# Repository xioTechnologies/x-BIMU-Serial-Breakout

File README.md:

x-BIMU-Serial-Breakout
======================

x-BIMU serial breakout board

* FTDI compatible 6-way male header (x-BIMU UART inputs are 5 V tolerant)
* Pull-down resistor on CTS input means that hardware flow-control connections are not necessary
* 3.1 mm diameter mounting holes (position = 31 mm x 27 mm)
* All components are SMD and on top side only and no copper on bottom side allow PCB bottom to be adhered to surfaces without risk of damage

Version history
---------------

* **v1.1** CTS pull-down removed.  Bypass voltage regulator jumper
* **v1.0** Initial design

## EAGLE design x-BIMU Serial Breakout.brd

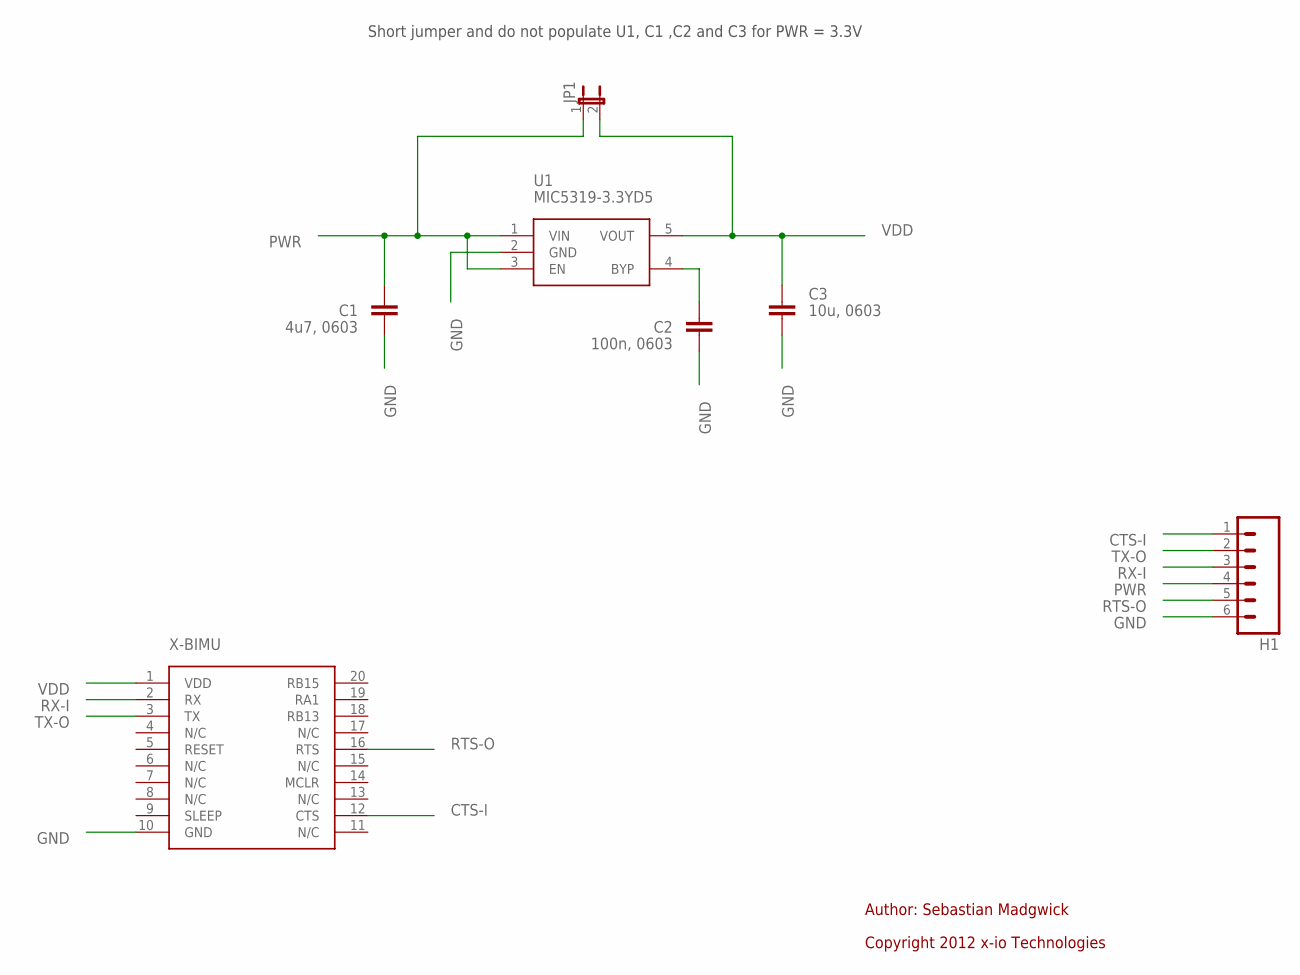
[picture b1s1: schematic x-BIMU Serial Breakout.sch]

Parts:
C1: 4u7, 0603; 0402-CAP
C2: 100n, 0603; 0402-CAP
C3: 10u, 0603; 0402-CAP
H1: M06SMD; 1X06-SMD
JP1: JUMPER-2SMD-NO; SJ_2S-NO
U1: MIC5319-3.3YD5; SOT23-5
U2: X-BIMU; X-BIMU_SMD

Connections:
CTS-I: H1.1, U2.12 (CTS)
GND: C1.2, C2.2, C3.2, H1.6, U1.2 (GND), U2.10 (GND)
unnamed: C2.1, U1.4 (BYP)
PWR: C1.1, H1.4, JP1.1, U1.1 (VIN), U1.3 (EN)
RTS-O: H1.5, U2.16 (RTS)
RX-I: H1.3, U2.2 (RX)
TX-O: H1.2, U2.3 (TX)
VDD: C3.1, JP1.2, U1.5 (VOUT), U2.1 (VDD)

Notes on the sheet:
Author: Sebastian Madgwick
Copyright 2012 x-io Technologies
Short jumper and do not populate U1, C1 ,C2 and C3 for PWR = 3.3V

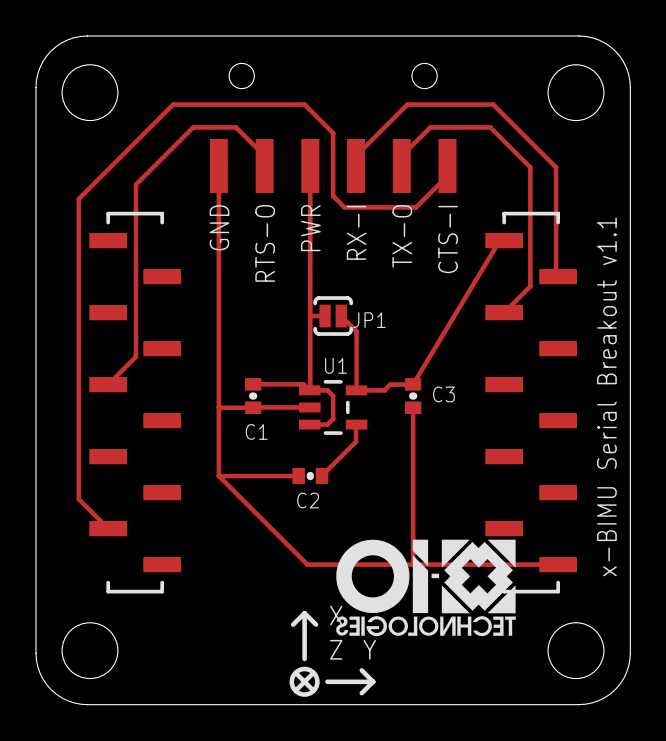
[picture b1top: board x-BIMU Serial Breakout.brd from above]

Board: 2 copper layers, 33.0 x 37.1 mm, 9 parts (1 on the bottom side), 8 nets.

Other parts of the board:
U$1: X-IO_TECHNOLOGIES_LOGO_10MM_BOTTOM
U$2: OSHW_LOGO_6MM_BOTTOM

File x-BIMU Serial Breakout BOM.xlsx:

Name | Qty | Device
U1 | 1 | MIC5319-3.3YD5
C1 | 1 | 4u7, 0603
C2 | 1 | 100n, 0603
C3 | 1 | 10u, 0603
H1 | 1 | 6-way SMD R/A header
x-BIMU | 1 | 10-way SMD socket (x2)

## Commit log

2013-04-07 1k CTS pull-down to account for internal pull-up
2013-06-27 Remove CTS pull-down. Add regulator bypass jumper
2013-06-28 Include BOM
